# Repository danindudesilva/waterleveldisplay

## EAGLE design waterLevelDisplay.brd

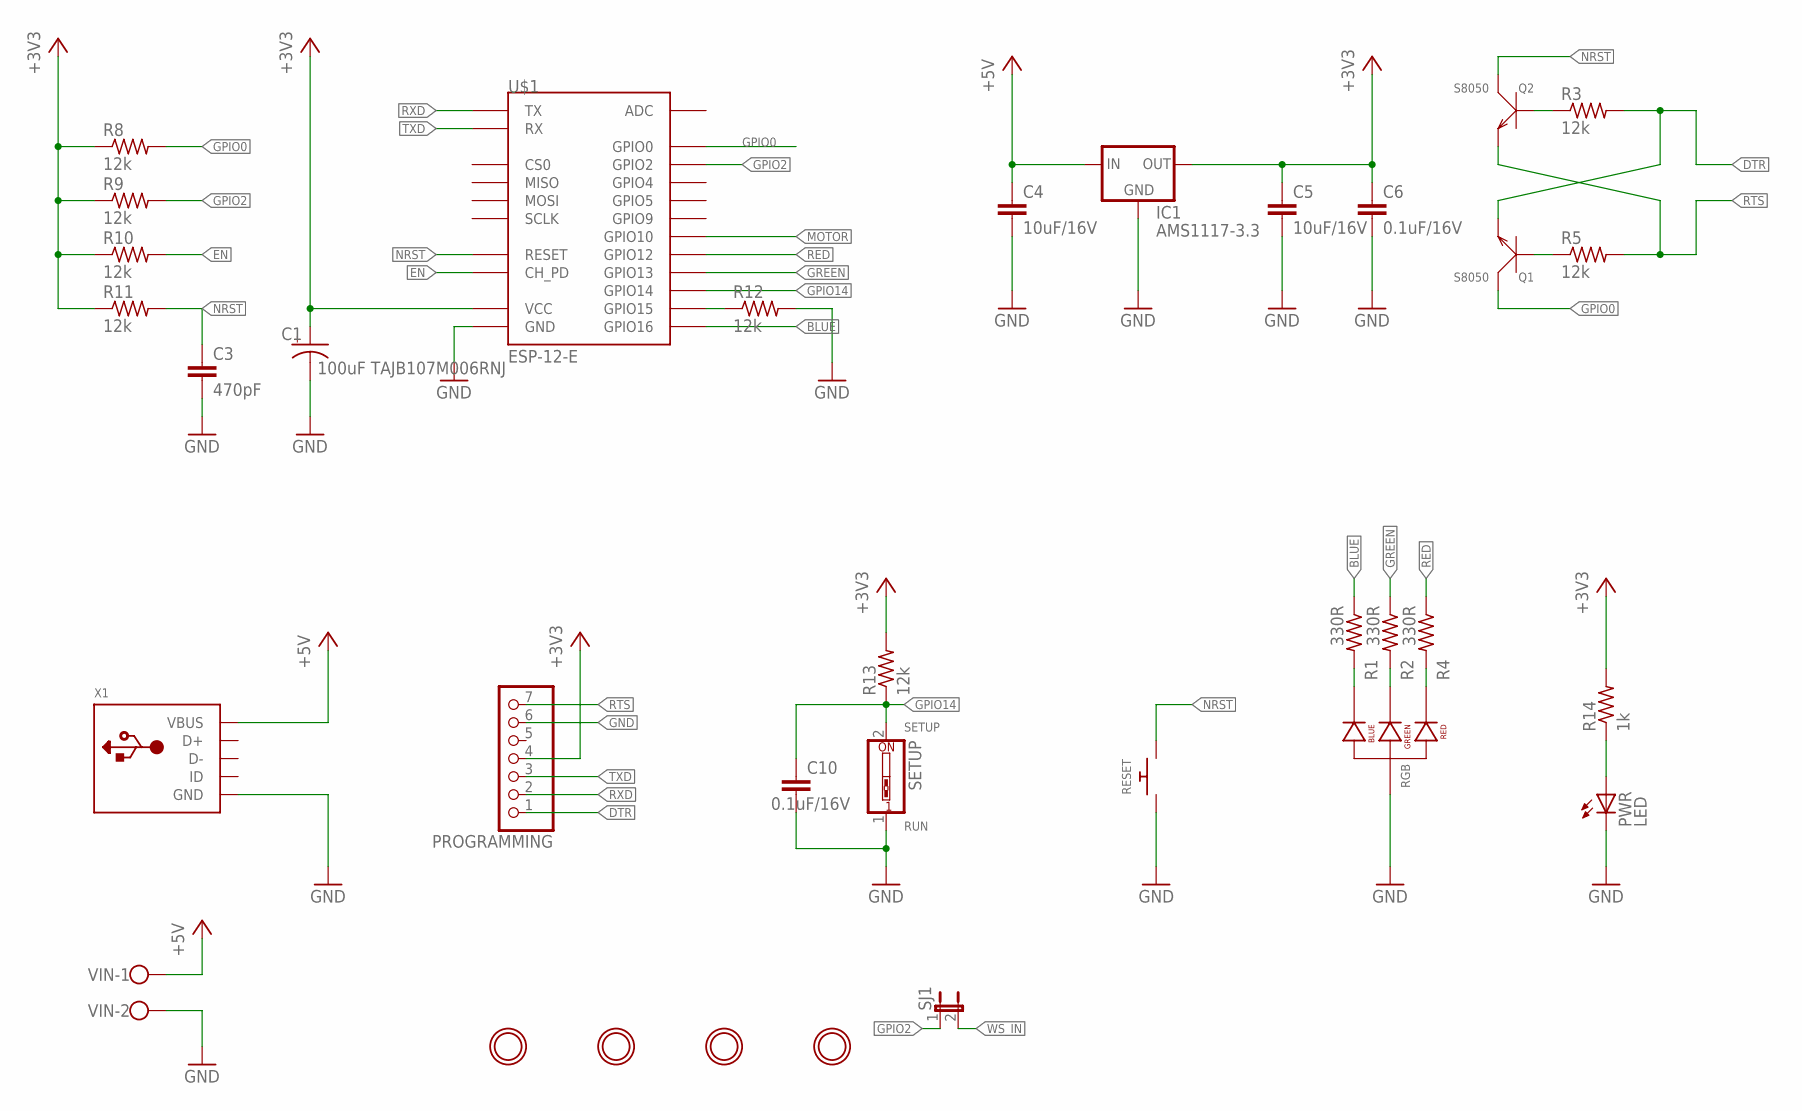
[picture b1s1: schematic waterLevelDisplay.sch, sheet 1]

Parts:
C1: 100uF TAJB107M006RNJ; A/3216-18R
C3: 470pF; C0805K
C4, C5: 10uF/16V; C0805K
C6, C10: 0.1uF/16V; C0805K
IC1: AMS1117-3.3; SOT223
PROGRAMMING: PINHD-1X7; 1X07
PWR: LED; CHIP-LED0805
Q1, Q2: S8050; SOT-23
R1, R2, R4: 330R; M0805
R3, R5, R8, R9, R10, R11, R12, R13: 12k; M0805
R14: 1k; M0805
RESET: SWITCH_PUSHBUTTONEVQ-PE; TACT_PANA-EVQ
RGB: LED-RGB-CA-THRUCLEAR; LED-RGB-THRU
SETUP: SW_DIP-1; EDG-01
SJ1: SPARKFUN-PASSIVES_JUMPER-PTH-2-NC; SPARKFUN-PASSIVES_PTH-JUMPER-NC_BOTTOM_NO_SILK
U$1: ESP-12-E
U$3, U$4, U$5, U$6: MOUNTINGHOLE2.5; MOUNTINGHOLE_2.5_PLATED
VIN: W237-102
X1: USB_MICRO_20329_V2; 4UCONN_20329_V2

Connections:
+3V3: C1.+, C5.1, C6.1, IC1.2 (OUT), PROGRAMMING.4, R8.1, R9.1, R10.1, R11.1, R13.2, R14.2, U$1.VCC; also elsewhere on the board
+5V: C4.1, IC1.3 (IN), VIN.1, X1.VBUS; also elsewhere on the board
BLUE: R1.1, U$1.GPIO16
DTR: PROGRAMMING.1, Q1.2 (E), R3.2
EN: R10.2, U$1.CH_PD
GND: C1.-, C3.2, C4.2, C5.2, C6.2, C10.2, IC1.1 (GND), PROGRAMMING.6, PWR.C, R12.2, RESET.P$1, RGB.2 (ANODE), SETUP.1, U$1.GND, VIN.2, X1.BASE@1 (GND), X1.BASE@2 (GND), X1.GND, X1.SPRT@1 (GND), X1.SPRT@2 (GND), X1.SPRT@3 (GND), X1.SPRT@4 (GND); also elsewhere on the board
GPIO0: Q1.3 (C), R8.2, U$1.GPIO0
GPIO2: R9.2, SJ1.1, U$1.GPIO2
GPIO14: C10.1, R13.1, SETUP.2, U$1.GPIO14
GREEN: R2.1, U$1.GPIO13
MOTOR: U$1.GPIO10; also elsewhere on the board
unnamed: Q2.1 (B), R3.1
unnamed: Q1.1 (B), R5.1
unnamed: R12.1, U$1.GPIO15
unnamed: PWR.A, R14.1
unnamed: R4.2, RGB.1 (RED_CATHODE)
unnamed: R2.2, RGB.3 (GREEN_CATHODE)
unnamed: R1.2, RGB.4 (BLUE_CATHODE)
NRST: C3.1, Q2.3 (C), R11.2, RESET.P$2, U$1.RESET
RED: R4.1, U$1.GPIO12
RTS: PROGRAMMING.7, Q2.2 (E), R5.2
RXD: PROGRAMMING.2, U$1.TX
TXD: PROGRAMMING.3, U$1.RX
WS_IN: SJ1.2; also elsewhere on the board

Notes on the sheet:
RUN
SETUP

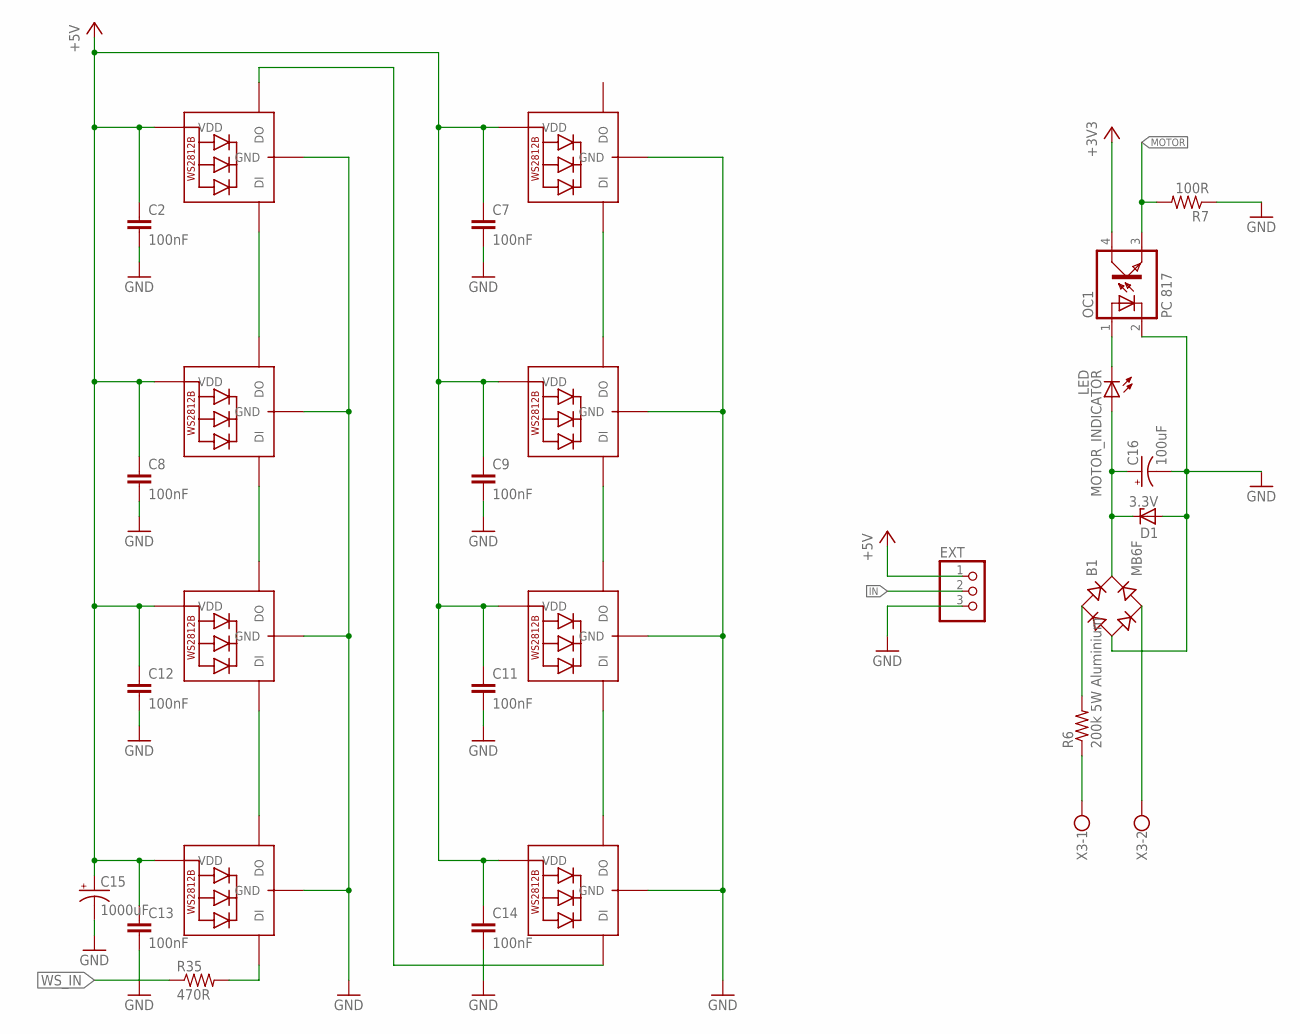
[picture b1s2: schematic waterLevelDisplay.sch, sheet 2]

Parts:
B1: MB6F; SOIC-4
C2, C7, C8, C9, C11, C12, C13, C14: 100nF; C0805K
C15: 1000uF; E5-10,5
C16: 100uF; E2,5-7
D1: 3.3V; ZDIO-7.5
EXT: PINHD-1X3; 1X03
LED1, LED2, LED3, LED4, LED5, LED6, LED7, LED8: WS2812B5050; WS2812B
MOTOR_INDICATOR: LED; CHIP-LED0805
OC1: PC 817; DIP4
R6: 200k 5W Aluminium; 0617/22
R7: 100R; M0805
R35: 470R; M0805
X3: W237-102

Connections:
+3V3: OC1.4 (COL); also elsewhere on the board
+5V: C2.1, C7.1, C8.1, C9.1, C11.1, C12.1, C13.1, C14.1, C15.+, EXT.1, LED1.1-VDD (VDD), LED2.1-VDD (VDD), LED3.1-VDD (VDD), LED4.1-VDD (VDD), LED5.1-VDD (VDD), LED6.1-VDD (VDD), LED7.1-VDD (VDD), LED8.1-VDD (VDD); also elsewhere on the board
GND: B1.-, C2.2, C7.2, C8.2, C9.2, C11.2, C12.2, C13.2, C14.2, C15.-, C16.-, D1.A, EXT.3, LED1.3-GND (GND), LED2.3-GND (GND), LED3.3-GND (GND), LED4.3-GND (GND), LED5.3-GND (GND), LED6.3-GND (GND), LED7.3-GND (GND), LED8.3-GND (GND), OC1.2 (C), R7.1; also elsewhere on the board
IN: EXT.2, LED8.4-DIN (DI), R35.2
MOTOR: OC1.3 (EMIT), R7.2; also elsewhere on the board
unnamed: R6.1, X3.1
unnamed: B1.~1 (AC1), R6.2
unnamed: B1.~2 (AC2), X3.2
unnamed: LED5.4-DIN (DI), LED8.2-DOUT (DO)
unnamed: LED3.4-DIN (DI), LED5.2-DOUT (DO)
unnamed: LED1.4-DIN (DI), LED3.2-DOUT (DO)
unnamed: LED1.2-DOUT (DO), LED7.4-DIN (DI)
unnamed: LED6.4-DIN (DI), LED7.2-DOUT (DO)
unnamed: LED4.4-DIN (DI), LED6.2-DOUT (DO)
unnamed: LED2.4-DIN (DI), LED4.2-DOUT (DO)
unnamed: B1.+, C16.+, D1.C, MOTOR_INDICATOR.A
unnamed: MOTOR_INDICATOR.C, OC1.1 (A)
WS_IN: R35.1; also elsewhere on the board

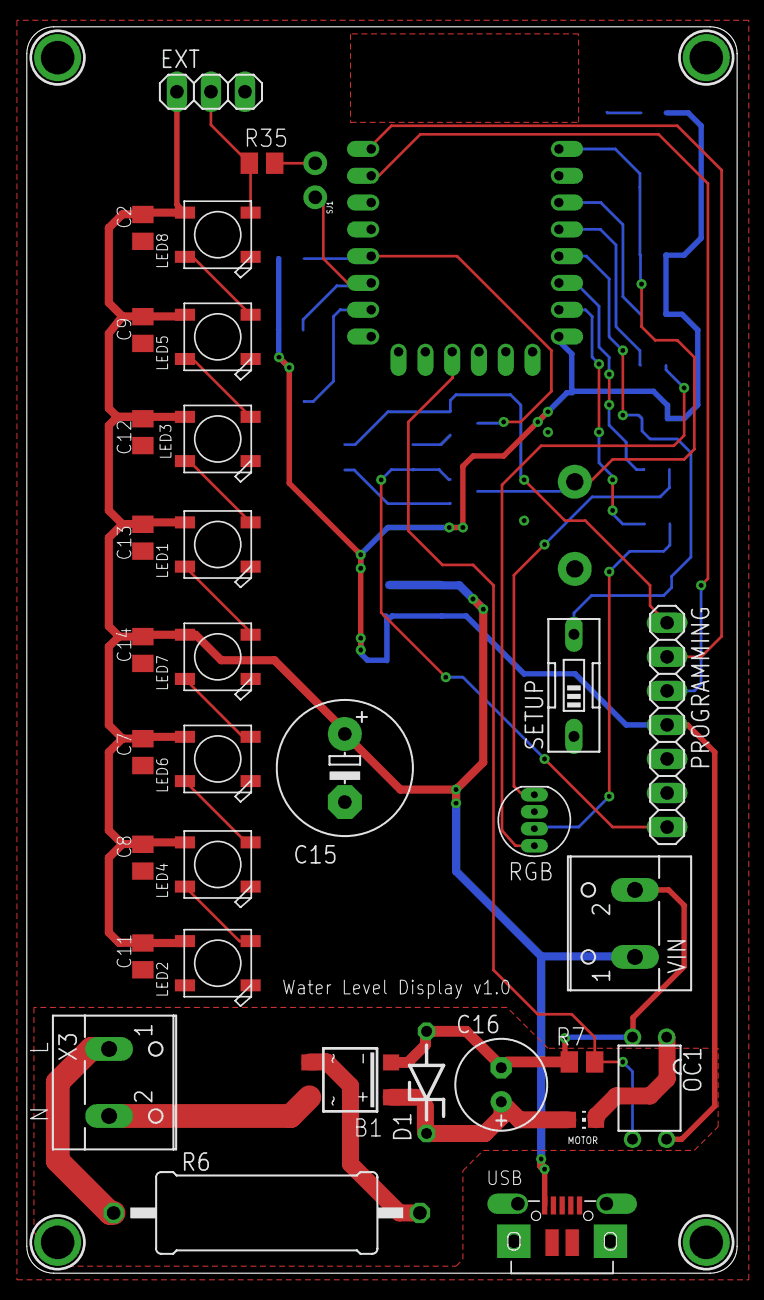
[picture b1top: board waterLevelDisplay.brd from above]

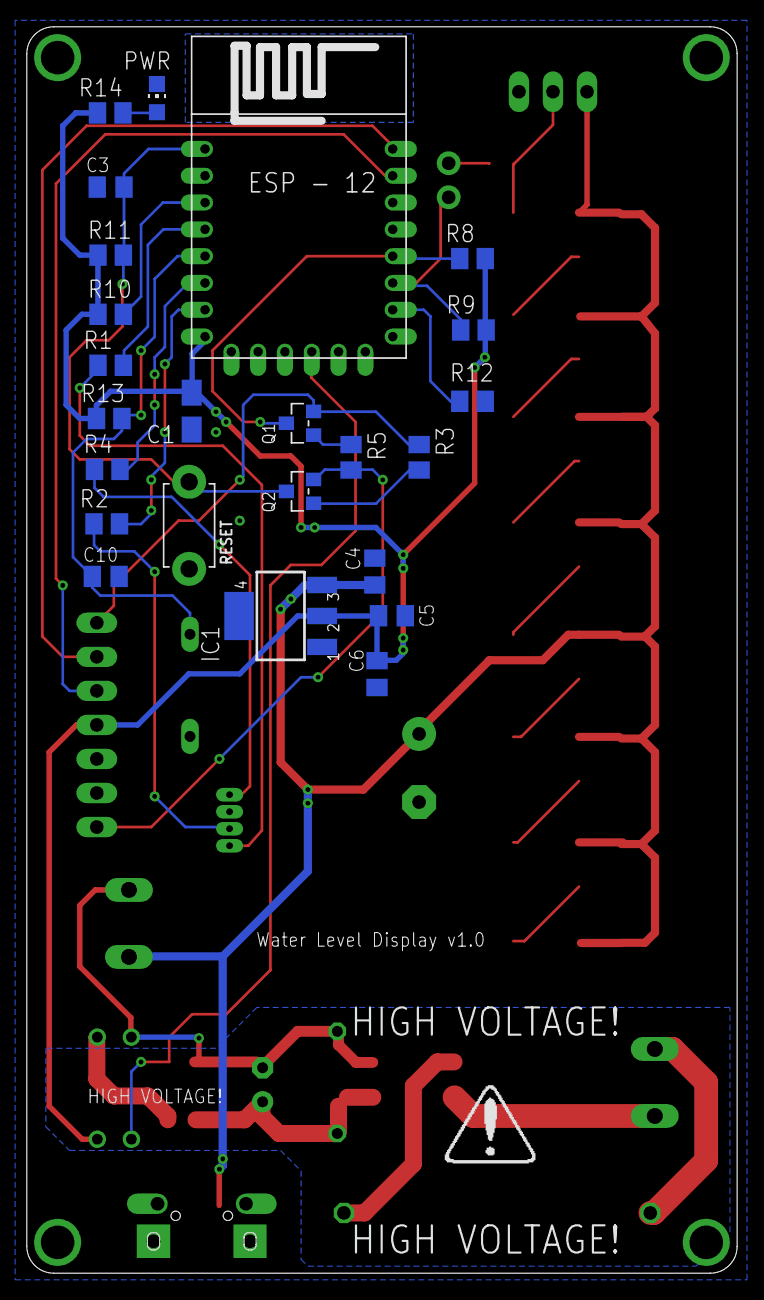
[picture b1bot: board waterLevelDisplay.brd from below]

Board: 2 copper layers, 53.0 x 93.0 mm, 61 parts (24 on the bottom side), 37 nets.

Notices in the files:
parts and their libraries:
SparkFun-LED: Licensing: Creative Commons ShareAlike 4.0 International - https://creativecommons.org/licenses/by-sa/4.0
